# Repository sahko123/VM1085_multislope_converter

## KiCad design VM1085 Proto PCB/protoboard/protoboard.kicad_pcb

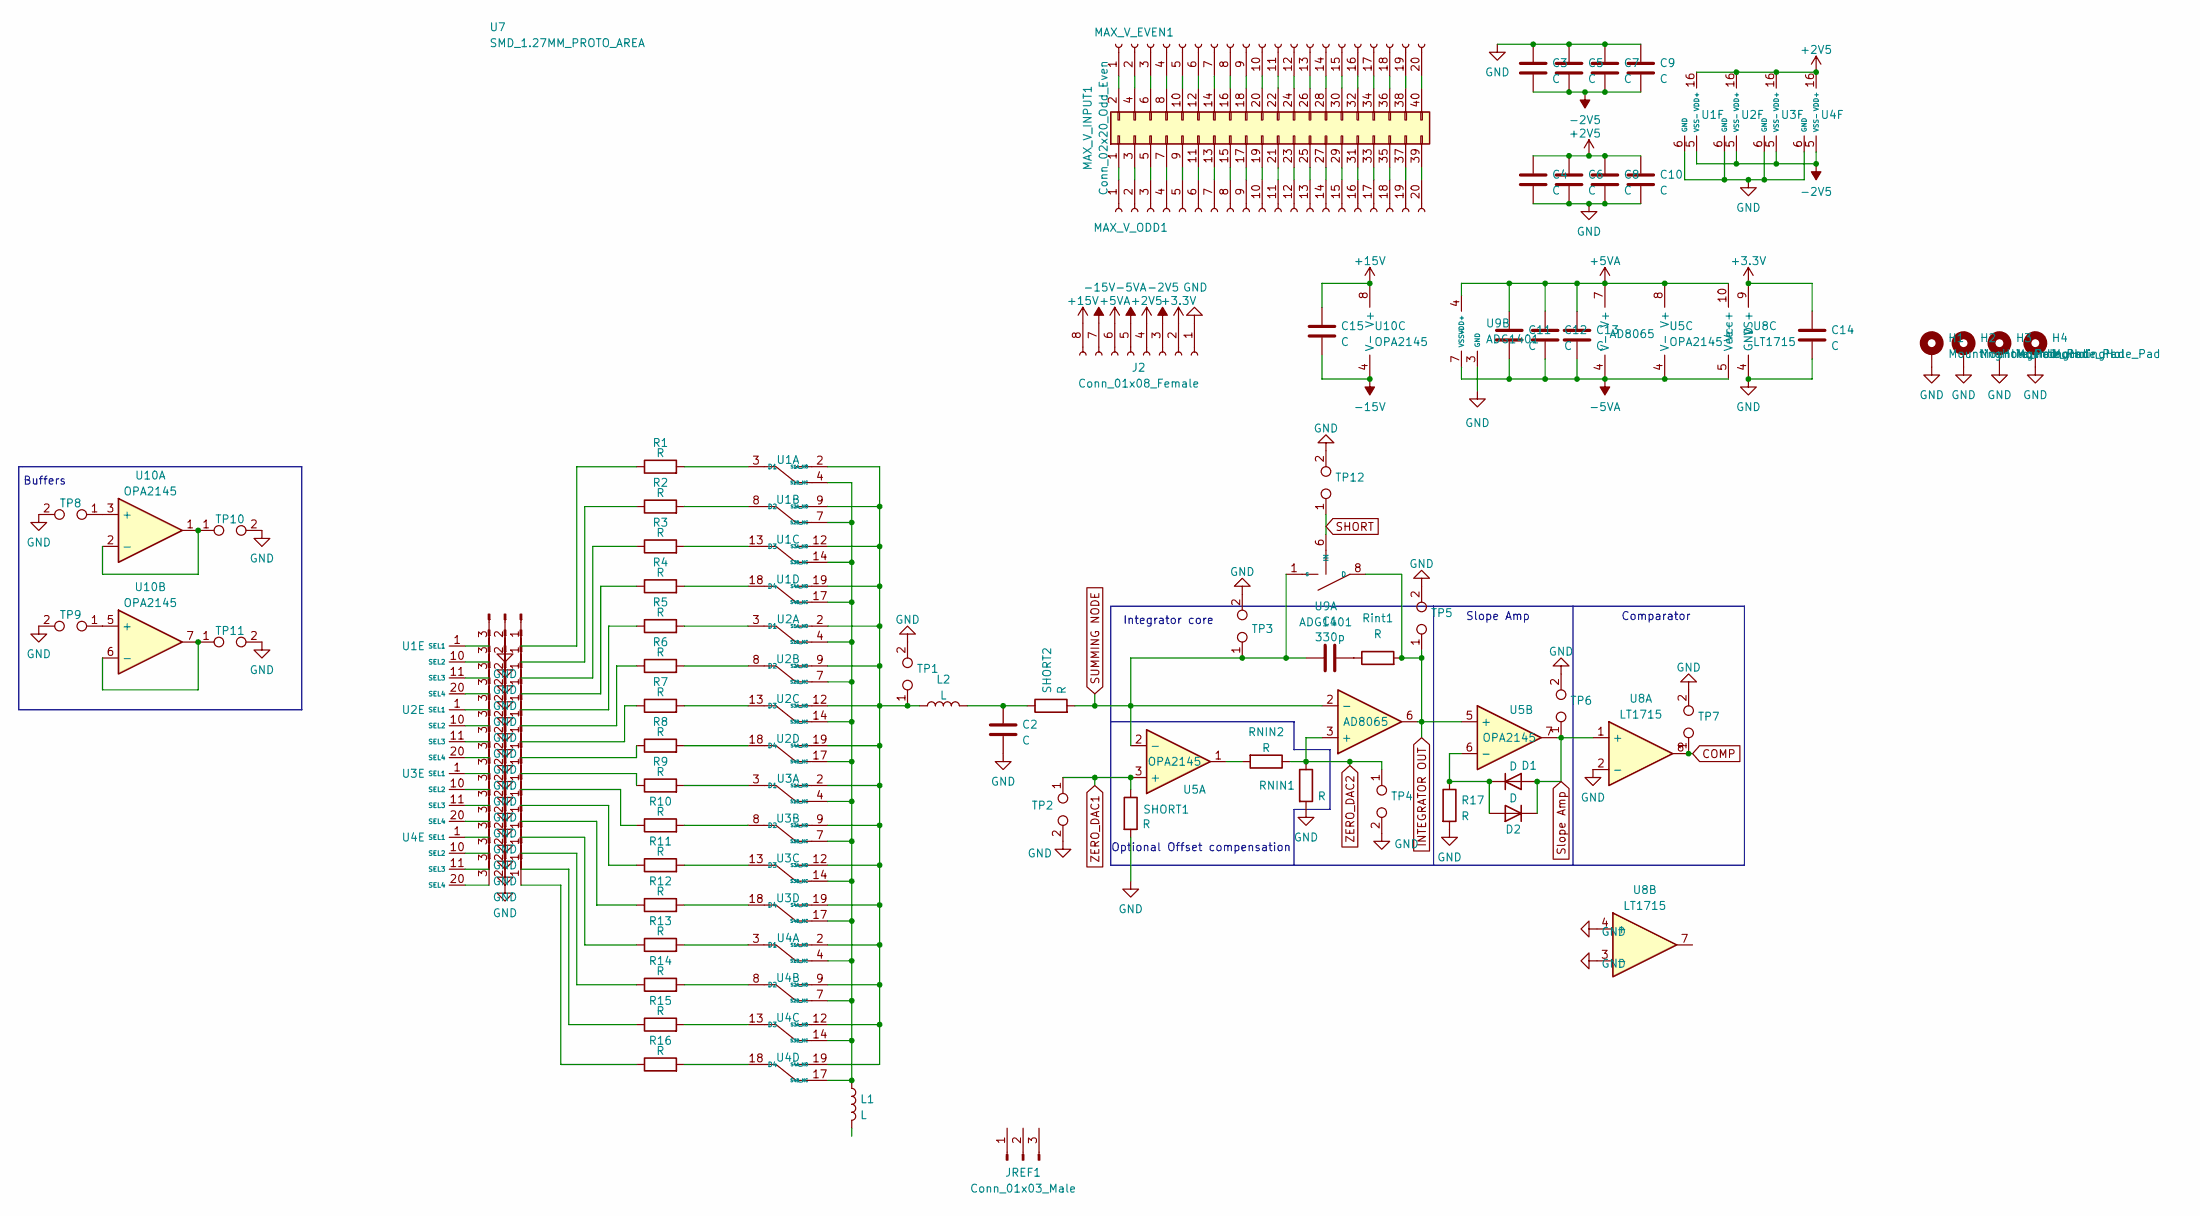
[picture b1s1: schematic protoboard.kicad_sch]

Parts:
C1: 330p; C_0603_1608Metric_Pad1.08x0.95mm_HandSolder
C2, C3, C4, C5, C6, C7, C8, C9, C10, C11, C12, C13, C14, C15: C; C_0603_1608Metric_Pad1.08x0.95mm_HandSolder
D1, D2: D; D_0603_1608Metric
H1, H2, H3, H4: MountingHole_Pad
J1, J3, J4, J5, J6, J7, J8, J9, J10, J11, J12, J13, J14, J15, J16, J17: Conn_01x03_Male; PinHeader_1x03_P2.54mm_Vertical
J2: Conn_01x08_Female; PinHeader_1x08_P2.54mm_Vertical
JREF1: Conn_01x03_Male
L1, L2: L; C_0805_2012Metric_Pad1.18x1.45mm_HandSolder
MAX_V_EVEN1: Conn_01x20_Female; PinHeader_1x20_P2.54mm_Vertical
MAX_V_INPUT1: Conn_02x20_Odd_Even; PinHeader_2x20_P2.54mm_Vertical
MAX_V_ODD1: Conn_01x20_Female; PinHeader_1x20_P2.54mm_Vertical
R1, R2, R3, R4, R5, R6, R7, R8, R9, R10, R11, R12, R13, R14, R15, R16: R; Resistor_multipad
R17: R; R_0805_2012Metric_Pad1.20x1.40mm_HandSolder
RNIN1, RNIN2: R; R_0805_2012Metric_Pad1.20x1.40mm_HandSolder
Rint1: R; R_0805_2012Metric_Pad1.20x1.40mm_HandSolder
SHORT1, SHORT2: R; R_0805_2012Metric_Pad1.20x1.40mm_HandSolder
TP1, TP2, TP3, TP4, TP5, TP6, TP7, TP8, TP9, TP10, TP11, TP12: TestPoint_2Pole; PinHeader_1x02_P2.54mm_Vertical
U1, U2, U3, U4: TMUX1134; TSSOP-20_4.4x6.5mm_P0.65mm
U5, U10: OPA2145; SOP-8_3.9x4.9mm_P1.27mm
U6: AD8065; SOIC-8_3.9x4.9mm_P1.27mm
U7: SMD_1.27MM_PROTO_AREA; SMD_1.27_proto_area
U8: LT1715; MSOP-10_3x3mm_P0.5mm
U9: ADG1401; MSOP-8_3x3mm_P0.65mm

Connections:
+2V5: C4.1, C6.1, C8.1, C10.1, J2.4, U1.16 (VDD+), U2.16 (VDD+), U3.16 (VDD+), U4.16 (VDD+)
+3V3: C14.1, J2.2, U8.9 (VS+)
+5VA: C11.1, C12.1, C13.1, J2.6, U5.8 (V+), U6.7 (V+), U8.10 (Vcc+), U9.4 (VDD+)
+15V: C15.1, J2.8, U10.8 (V+)
-2V5: C3.2, C5.2, C7.2, C9.2, J2.3, U1.5 (VSS-), U2.5 (VSS-), U3.5 (VSS-), U4.5 (VSS-)
-5VA: C11.2, C12.2, C13.2, J2.5, U5.4 (V-), U6.4 (V-), U8.5 (Vee-), U9.7 (VSS-)
-15V: C15.2, J2.7, U10.4 (V-)
COMP: TP7.1, U8.8
GND: C2.2, C3.1, C4.2, C5.1, C6.2, C7.1, C8.2, C9.1, C10.2, C14.2, H1.1, H2.1, H3.1, H4.1, J1.2, J2.1, J3.2, J4.2, J5.2, J6.2, J7.2, J8.2, J9.2, J10.2, J11.2, J12.2, J13.2, J14.2, J15.2, J16.2, J17.2, R17.2, RNIN1.2, SHORT1.2, TP1.2, TP2.2, TP3.2, TP4.2, TP5.2, TP6.2, TP7.2, TP8.2, TP9.2, TP10.2, TP11.2, TP12.2, U1.6 (GND), U2.6 (GND), U3.6 (GND), U4.6 (GND), U8.2 (-), U8.3 (-), U8.4 (GND), U9.3 (GND)
INTEGRATOR OUT: Rint1.2, TP5.1, U5.5 (+), U6.6, U9.8 (D)
unnamed: C1.2, Rint1.1
unnamed: C2.1, L2.2, SHORT2.1
unnamed: D1.1 (K), D2.2 (A), R17.1, U5.6 (-)
unnamed: J1.1, R1.1
unnamed: J1.3, U1.1 (SEL1)
unnamed: J3.1, R2.1
unnamed: J3.3, U1.10 (SEL2)
unnamed: J4.1, R3.1
unnamed: J4.3, U1.11 (SEL3)
unnamed: J5.1, R4.1
unnamed: J5.3, U1.20 (SEL4)
unnamed: J6.1, R5.1
unnamed: J6.3, U2.1 (SEL1)
unnamed: J7.1, R6.1
unnamed: J7.3, U2.10 (SEL2)
unnamed: J8.1, R7.1
unnamed: J8.3, U2.11 (SEL3)
unnamed: J9.1, R8.1
unnamed: J9.3, U2.20 (SEL4)
unnamed: J10.1, R9.1
unnamed: J10.3, U3.1 (SEL1)
unnamed: J11.1, R10.1
unnamed: J11.3, U3.10 (SEL2)
unnamed: J12.1, R11.1
unnamed: J12.3, U3.11 (SEL3)
unnamed: J13.1, R12.1
unnamed: J13.3, U3.20 (SEL4)
unnamed: J14.1, R13.1
unnamed: J14.3, U4.1 (SEL1)
unnamed: J15.1, R14.1
unnamed: J15.3, U4.10 (SEL2)
unnamed: J16.1, R15.1
unnamed: J16.3, U4.11 (SEL3)
unnamed: J17.1, R16.1
unnamed: J17.3, U4.20 (SEL4)
unnamed: L1.1, U1.4 (S1B_NC), U1.7 (S2B_NC), U1.14 (S3B_NC), U1.17 (S4B_NC), U2.4 (S1B_NC), U2.7 (S2B_NC), U2.14 (S3B_NC), U2.17 (S4B_NC), U3.4 (S1B_NC), U3.7 (S2B_NC), U3.14 (S3B_NC), U3.17 (S4B_NC), U4.4 (S1B_NC), U4.7 (S2B_NC), U4.14 (S3B_NC), U4.17 (S4B_NC)
unnamed: L2.1, TP1.1, U1.2 (S1A_NO), U1.9 (S2A_NO), U1.12 (S3A_NO), U1.19 (S4A_NO), U2.2 (S1A_NO), U2.9 (S2A_NO), U2.12 (S3A_NO), U2.19 (S4A_NO), U3.2 (S1A_NO), U3.9 (S2A_NO), U3.12 (S3A_NO), U3.19 (S4A_NO), U4.2 (S1A_NO), U4.9 (S2A_NO), U4.12 (S3A_NO), U4.19 (S4A_NO)
unnamed: MAX_V_EVEN1.1, MAX_V_INPUT1.2
unnamed: MAX_V_EVEN1.2, MAX_V_INPUT1.4
unnamed: MAX_V_EVEN1.3, MAX_V_INPUT1.6
unnamed: MAX_V_EVEN1.4, MAX_V_INPUT1.8
unnamed: MAX_V_EVEN1.5, MAX_V_INPUT1.10
unnamed: MAX_V_EVEN1.6, MAX_V_INPUT1.12
unnamed: MAX_V_EVEN1.7, MAX_V_INPUT1.14
unnamed: MAX_V_EVEN1.8, MAX_V_INPUT1.16
unnamed: MAX_V_EVEN1.9, MAX_V_INPUT1.18
unnamed: MAX_V_EVEN1.10, MAX_V_INPUT1.20
unnamed: MAX_V_EVEN1.11, MAX_V_INPUT1.22
unnamed: MAX_V_EVEN1.12, MAX_V_INPUT1.24
unnamed: MAX_V_EVEN1.13, MAX_V_INPUT1.26
unnamed: MAX_V_EVEN1.14, MAX_V_INPUT1.28
unnamed: MAX_V_EVEN1.15, MAX_V_INPUT1.30
unnamed: MAX_V_EVEN1.16, MAX_V_INPUT1.32
unnamed: MAX_V_EVEN1.17, MAX_V_INPUT1.34
unnamed: MAX_V_EVEN1.18, MAX_V_INPUT1.36
unnamed: MAX_V_EVEN1.19, MAX_V_INPUT1.38
unnamed: MAX_V_EVEN1.20, MAX_V_INPUT1.40
unnamed: MAX_V_INPUT1.1, MAX_V_ODD1.1
unnamed: MAX_V_INPUT1.3, MAX_V_ODD1.2
unnamed: MAX_V_INPUT1.5, MAX_V_ODD1.3
unnamed: MAX_V_INPUT1.7, MAX_V_ODD1.4
unnamed: MAX_V_INPUT1.9, MAX_V_ODD1.5
unnamed: MAX_V_INPUT1.11, MAX_V_ODD1.6
unnamed: MAX_V_INPUT1.13, MAX_V_ODD1.7
unnamed: MAX_V_INPUT1.15, MAX_V_ODD1.8
unnamed: MAX_V_INPUT1.17, MAX_V_ODD1.9
unnamed: MAX_V_INPUT1.19, MAX_V_ODD1.10
unnamed: MAX_V_INPUT1.21, MAX_V_ODD1.11
unnamed: MAX_V_INPUT1.23, MAX_V_ODD1.12
unnamed: MAX_V_INPUT1.25, MAX_V_ODD1.13
unnamed: MAX_V_INPUT1.27, MAX_V_ODD1.14
unnamed: MAX_V_INPUT1.29, MAX_V_ODD1.15
unnamed: MAX_V_INPUT1.31, MAX_V_ODD1.16
unnamed: MAX_V_INPUT1.33, MAX_V_ODD1.17
unnamed: MAX_V_INPUT1.35, MAX_V_ODD1.18
unnamed: MAX_V_INPUT1.37, MAX_V_ODD1.19
unnamed: MAX_V_INPUT1.39, MAX_V_ODD1.20
unnamed: R1.2, U1.3 (D1)
unnamed: R2.2, U1.8 (D2)
unnamed: R3.2, U1.13 (D3)
unnamed: R4.2, U1.18 (D4)
unnamed: R5.2, U2.3 (D1)
unnamed: R6.2, U2.8 (D2)
unnamed: R7.2, U2.13 (D3)
unnamed: R8.2, U2.18 (D4)
unnamed: R9.2, U3.3 (D1)
unnamed: R10.2, U3.8 (D2)
unnamed: R11.2, U3.13 (D3)
unnamed: R12.2, U3.18 (D4)
unnamed: R13.2, U4.3 (D1)
unnamed: R14.2, U4.8 (D2)
unnamed: R15.2, U4.13 (D3)
unnamed: R16.2, U4.18 (D4)
unnamed: RNIN2.2, U5.1
unnamed: TP8.1, U10.3 (+)
unnamed: TP9.1, U10.5 (+)
unnamed: TP10.1, U10.1, U10.2 (-)
unnamed: TP11.1, U10.6 (-), U10.7
SHORT: TP12.1, U9.6 (IN)
SUMMING NODE: C1.1, SHORT2.2, TP3.1, U5.2 (-), U6.2 (-), U9.1 (S)
Slope Amp: D1.2 (A), D2.1 (K), TP6.1, U5.7, U8.1 (+)
ZERO_DAC1: SHORT1.1, TP2.1, U5.3 (+)
ZERO_DAC2: RNIN1.1, RNIN2.1, TP4.1, U6.3 (+)

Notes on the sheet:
Integrator core
Comparator
Optional Offset compensation
Buffers
Slope Amp

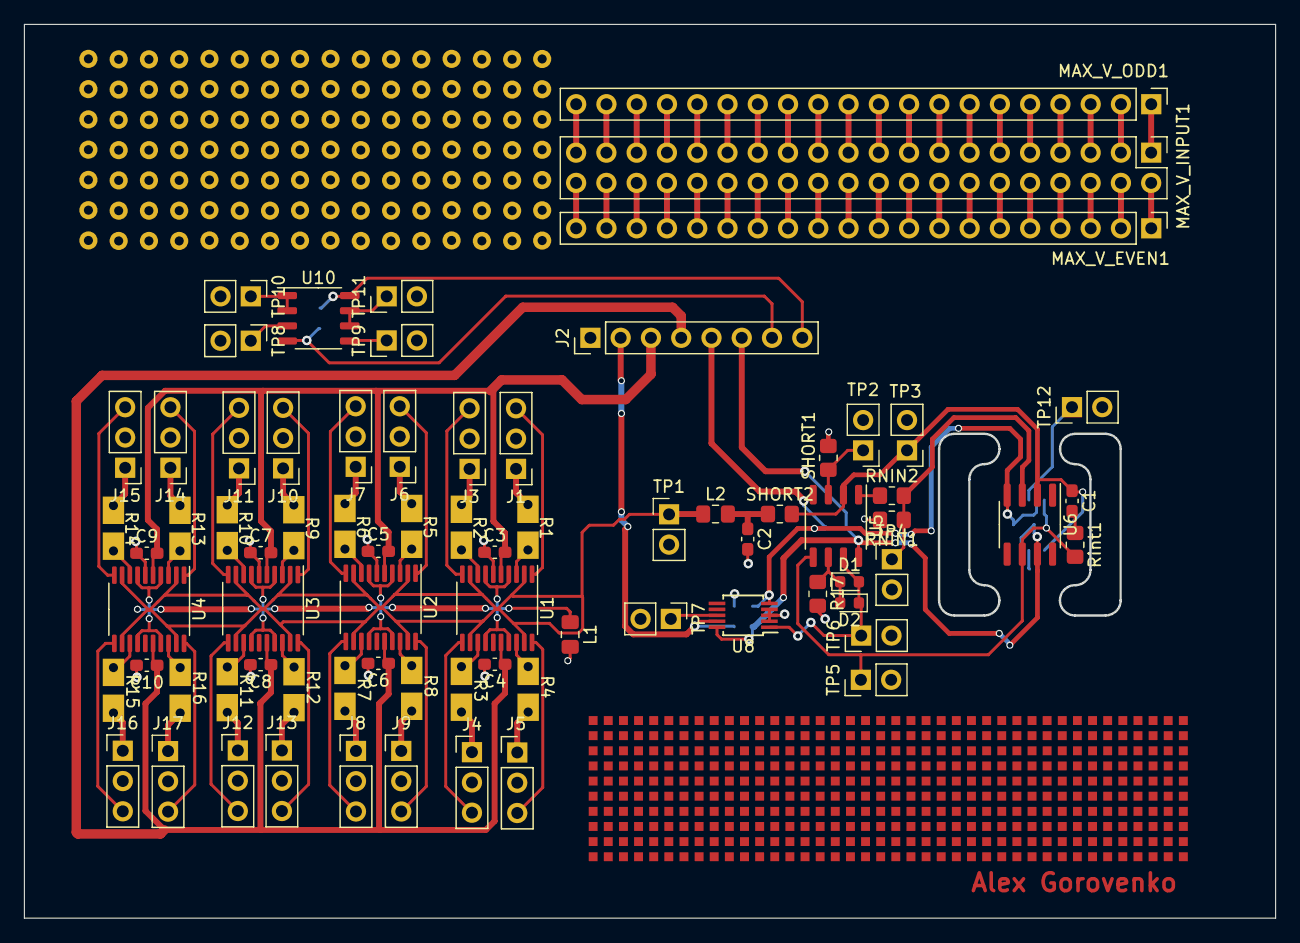
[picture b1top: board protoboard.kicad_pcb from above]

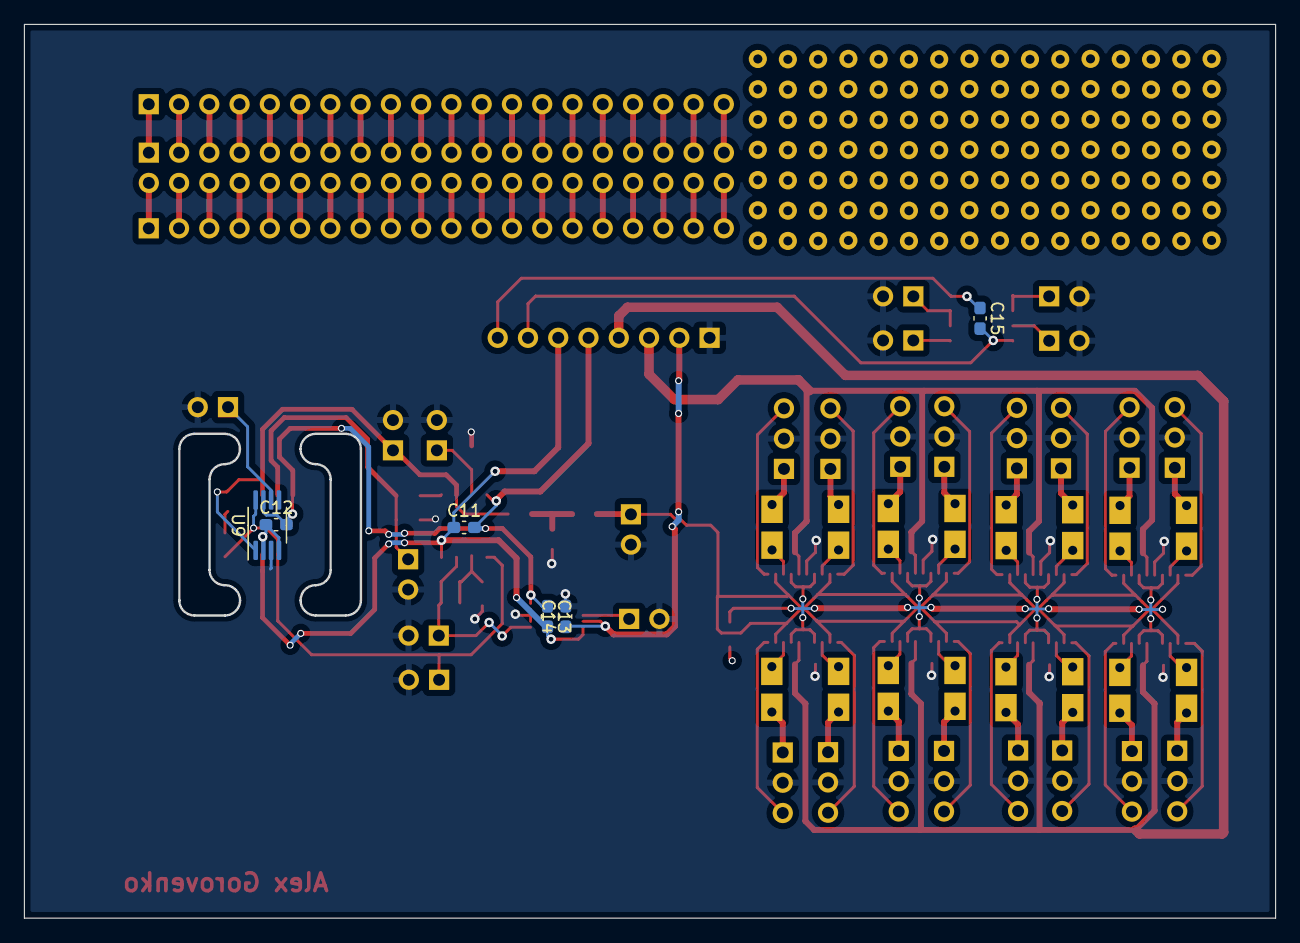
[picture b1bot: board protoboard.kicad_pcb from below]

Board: 2 copper layers, 104.9 x 74.9 mm, 83 parts (6 on the bottom side), 113 nets.

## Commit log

2023-02-24 first
2023-02-24 no message
2023-02-26 spi bus added from laptop
2023-02-26 kytdfhgf
2023-02-26 parallel bus add
2023-02-27 registers somewhat setup
2023-02-28 counter added as component
2023-03-01 multislope runup working i hope
2023-03-01 rundown added
2023-03-01 added arduino code for inguard microcontroller
2023-03-01 added write and read to cpld in inguard code
2023-03-01 pin map for dev board
2023-03-03 god knows
2023-03-04 full semi-final code
2023-03-05 proto board added to github
2023-03-05 scopy project added
2023-03-05 improvements in scopy project and code
2023-03-05 pcb backups
2023-03-06 first light
2023-03-06 added q comp
2023-03-06 inhouse sample timer added
2023-03-07 integral sample timing implemented
2023-03-07 adjustments
2023-03-07 removed qin comp
2023-03-07 restored 7 in 1 counter
2023-03-07 added early breakout
2023-03-08 re-added qin comp and sw_input0
2023-03-10 inguard micro reading succesful
2023-03-10 read slopes added
2023-03-11 added all slopes
2023-03-11 removed early breakout (was causing noise and possibly jumping)
2023-03-11 undid some stuff
2023-03-12 optimised early breakout to allow for exact sample times and no underflow
2023-03-12 added rpd1 signed handling
2023-03-13 HYPER PRIME COMMIT
2023-03-13 snapshot
2023-03-13 adding individual registers for all slope counters but runup
2023-03-17 pre-vhdl refresh for improvements to possible metastability
2023-03-18 stability build removed early breakout
2023-03-18 added better serial plotter exe
2023-03-21 added relay and calibration functions
2023-03-21 added 32 bit runup count and removal of redundant code
2023-05-07 rebase save
